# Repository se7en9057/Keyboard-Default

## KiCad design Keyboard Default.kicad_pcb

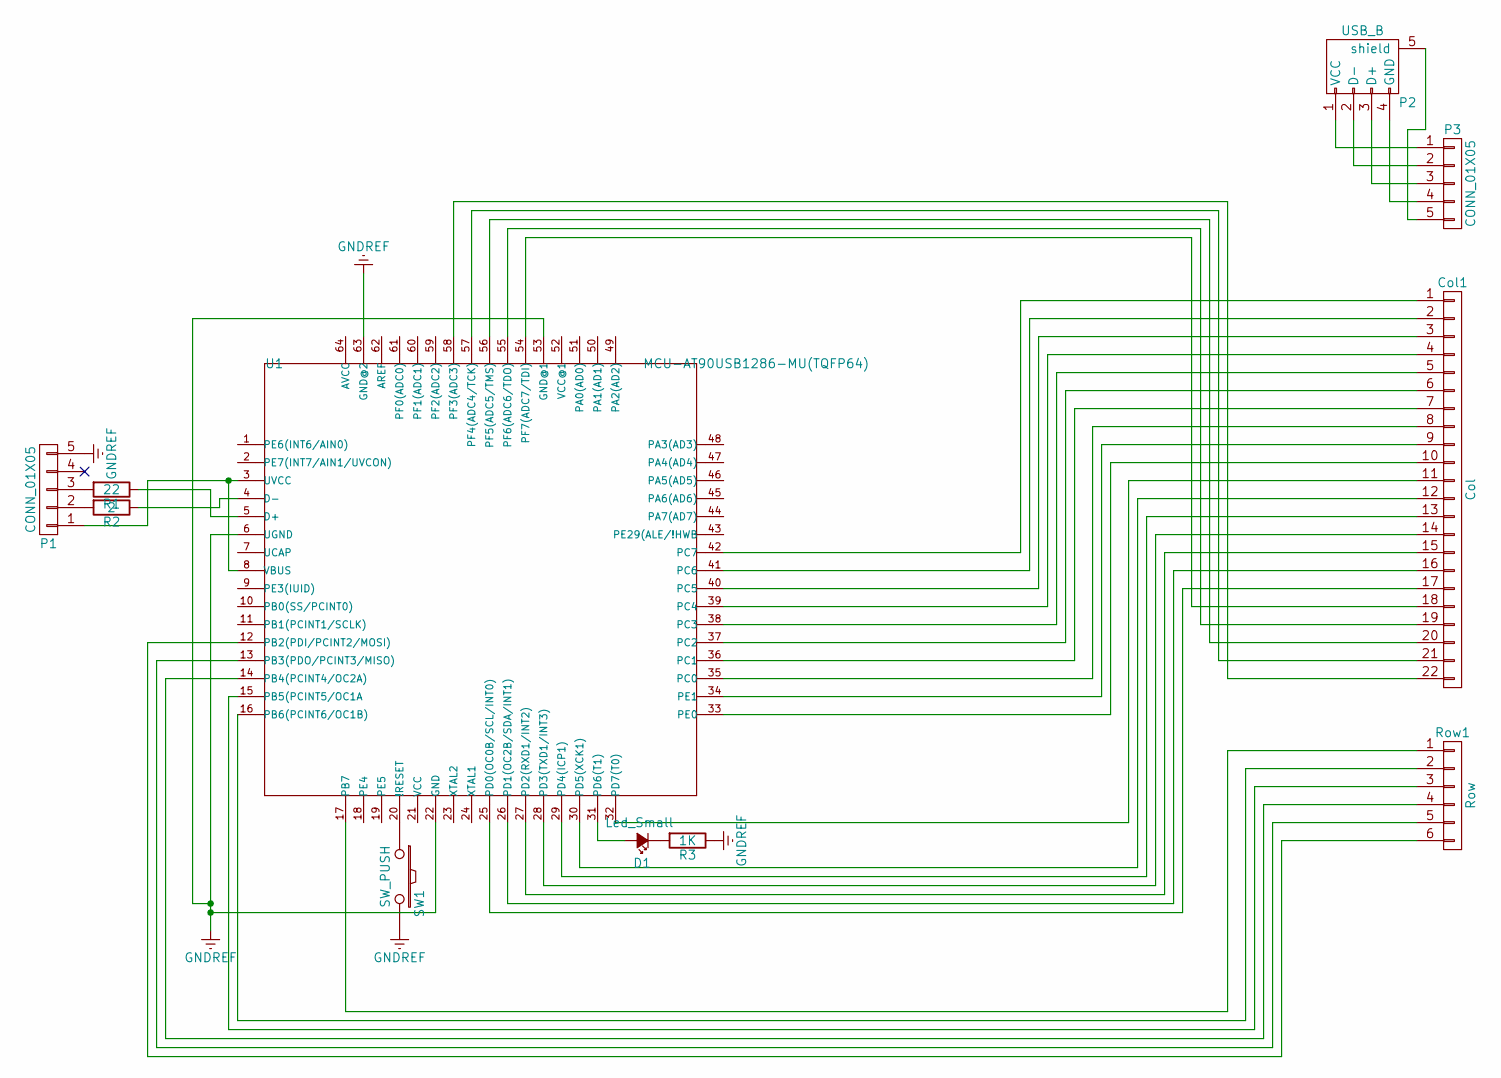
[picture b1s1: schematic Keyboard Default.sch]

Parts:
Col1: Col; Pin_Header_Straight_1x22
D1: Led_Small; LED_0603
P1, P3: CONN_01X05; Pin_Header_Straight_1x05
P2: USB_B; conn_usb_B_mini_smd
R1: 22; R_0805
R2: 2; R_0805
R3: 1K; R_0805
Row1: Row; Pin_Header_Straight_1x06
SW1: SW_PUSH; SW_SPST_B3U-1000P-B
U1: MCU-AT90USB1286-MU(TQFP64); TQFP64-0.8-14X14MM

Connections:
GNDREF: P1.5, R3.1, SW1.2, U1.6 (UGND), U1.22 (GND), U1.53 (GND@1), U1.63 (GND@2)
unnamed: Col1.1, U1.42 (PC7)
unnamed: Col1.2, U1.41 (PC6)
unnamed: Col1.3, U1.40 (PC5)
unnamed: Col1.4, U1.39 (PC4)
unnamed: Col1.5, U1.38 (PC3)
unnamed: Col1.6, U1.37 (PC2)
unnamed: Col1.7, U1.36 (PC1)
unnamed: Col1.8, U1.35 (PC0)
unnamed: Col1.9, U1.34 (PE1)
unnamed: Col1.10, U1.33 (PE0)
unnamed: Col1.11, U1.32 (PD7(T0))
unnamed: Col1.12, U1.30 (PD5(XCK1))
unnamed: Col1.13, U1.29 (PD4(ICP1))
unnamed: Col1.14, U1.28 (PD3(TXD1/INT3))
unnamed: Col1.15, U1.27 (PD2(RXD1/INT2))
unnamed: Col1.16, U1.26 (PD1(OC2B/SDA/INT1))
unnamed: Col1.17, U1.25 (PD0(OC0B/SCL/INT0))
unnamed: Col1.18, U1.54 (PF7(ADC7/TDI))
unnamed: Col1.19, U1.55 (PF6(ADC6/TDO))
unnamed: Col1.20, U1.56 (PF5(ADC5/TMS))
unnamed: Col1.21, U1.57 (PF4(ADC4/TCK))
unnamed: Col1.22, U1.58 (PF3(ADC3))
unnamed: D1.1 (K), R3.2
unnamed: D1.2 (A), U1.31 (PD6(T1))
unnamed: P1.1, U1.3 (UVCC), U1.8 (VBUS)
unnamed: P1.2, R2.2
unnamed: P1.3, R1.2
unnamed: P2.1 (VCC), P3.1
unnamed: P2.2 (D-), P3.2
unnamed: P2.3 (D+), P3.3
unnamed: P2.4 (GND), P3.4
unnamed: P2.5 (shield), P3.5
unnamed: R1.1, U1.5 (D+)
unnamed: R2.1, U1.4 (D-)
unnamed: Row1.1, U1.17 (PB7)
unnamed: Row1.2, U1.16 (PB6(PCINT6/OC1B))
unnamed: Row1.3, U1.15 (PB5(PCINT5/OC1A)
unnamed: Row1.4, U1.14 (PB4(PCINT4/OC2A))
unnamed: Row1.5, U1.13 (PB3(PDO/PCINT3/MISO))
unnamed: Row1.6, U1.12 (PB2(PDI/PCINT2/MOSI))
unnamed: SW1.1, U1.20 (!RESET)

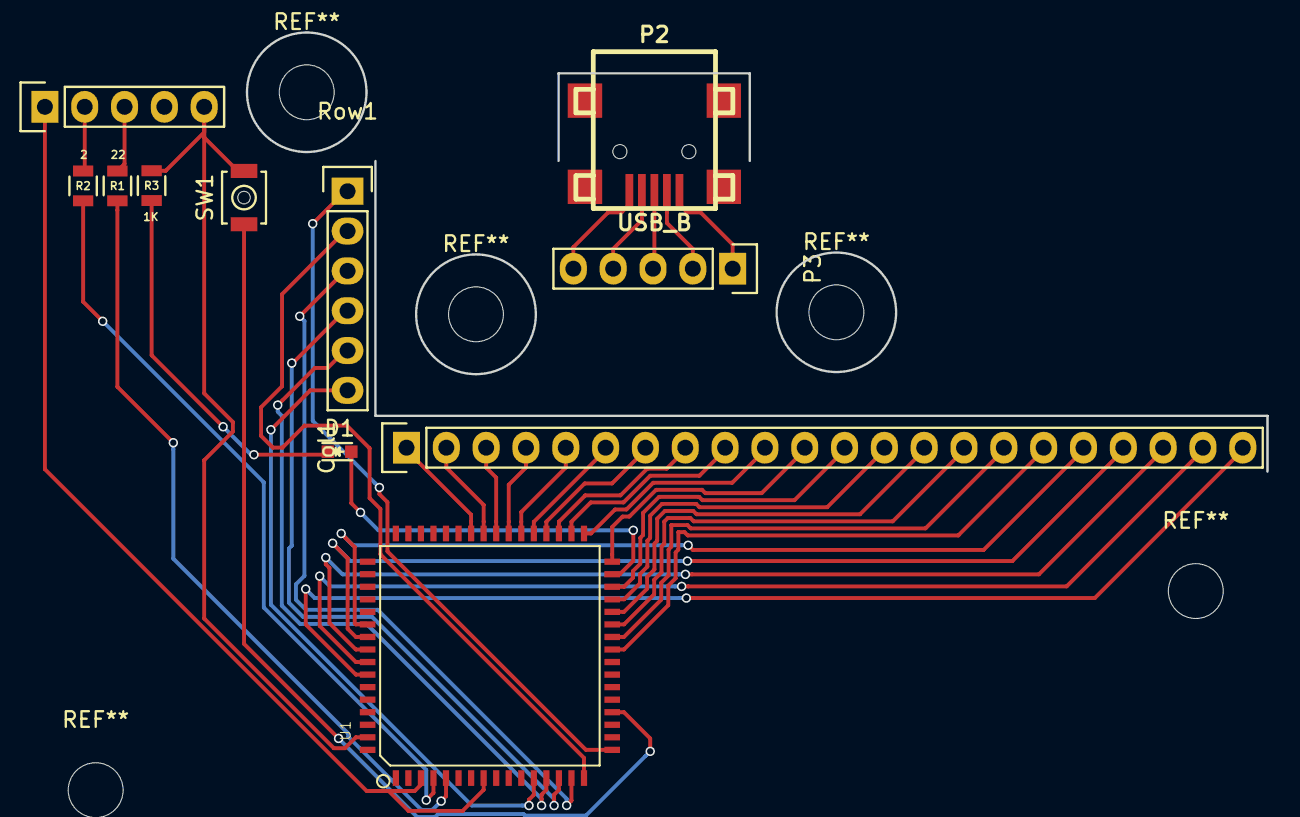
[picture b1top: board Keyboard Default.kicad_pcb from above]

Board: 2 copper layers, 11 parts (0 on the bottom side), 42 nets.

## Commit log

2016-06-17 :neckbeard: Added .gitattributes & .gitignore files
2016-06-17 KBfiles
2016-06-17 added capacitors
